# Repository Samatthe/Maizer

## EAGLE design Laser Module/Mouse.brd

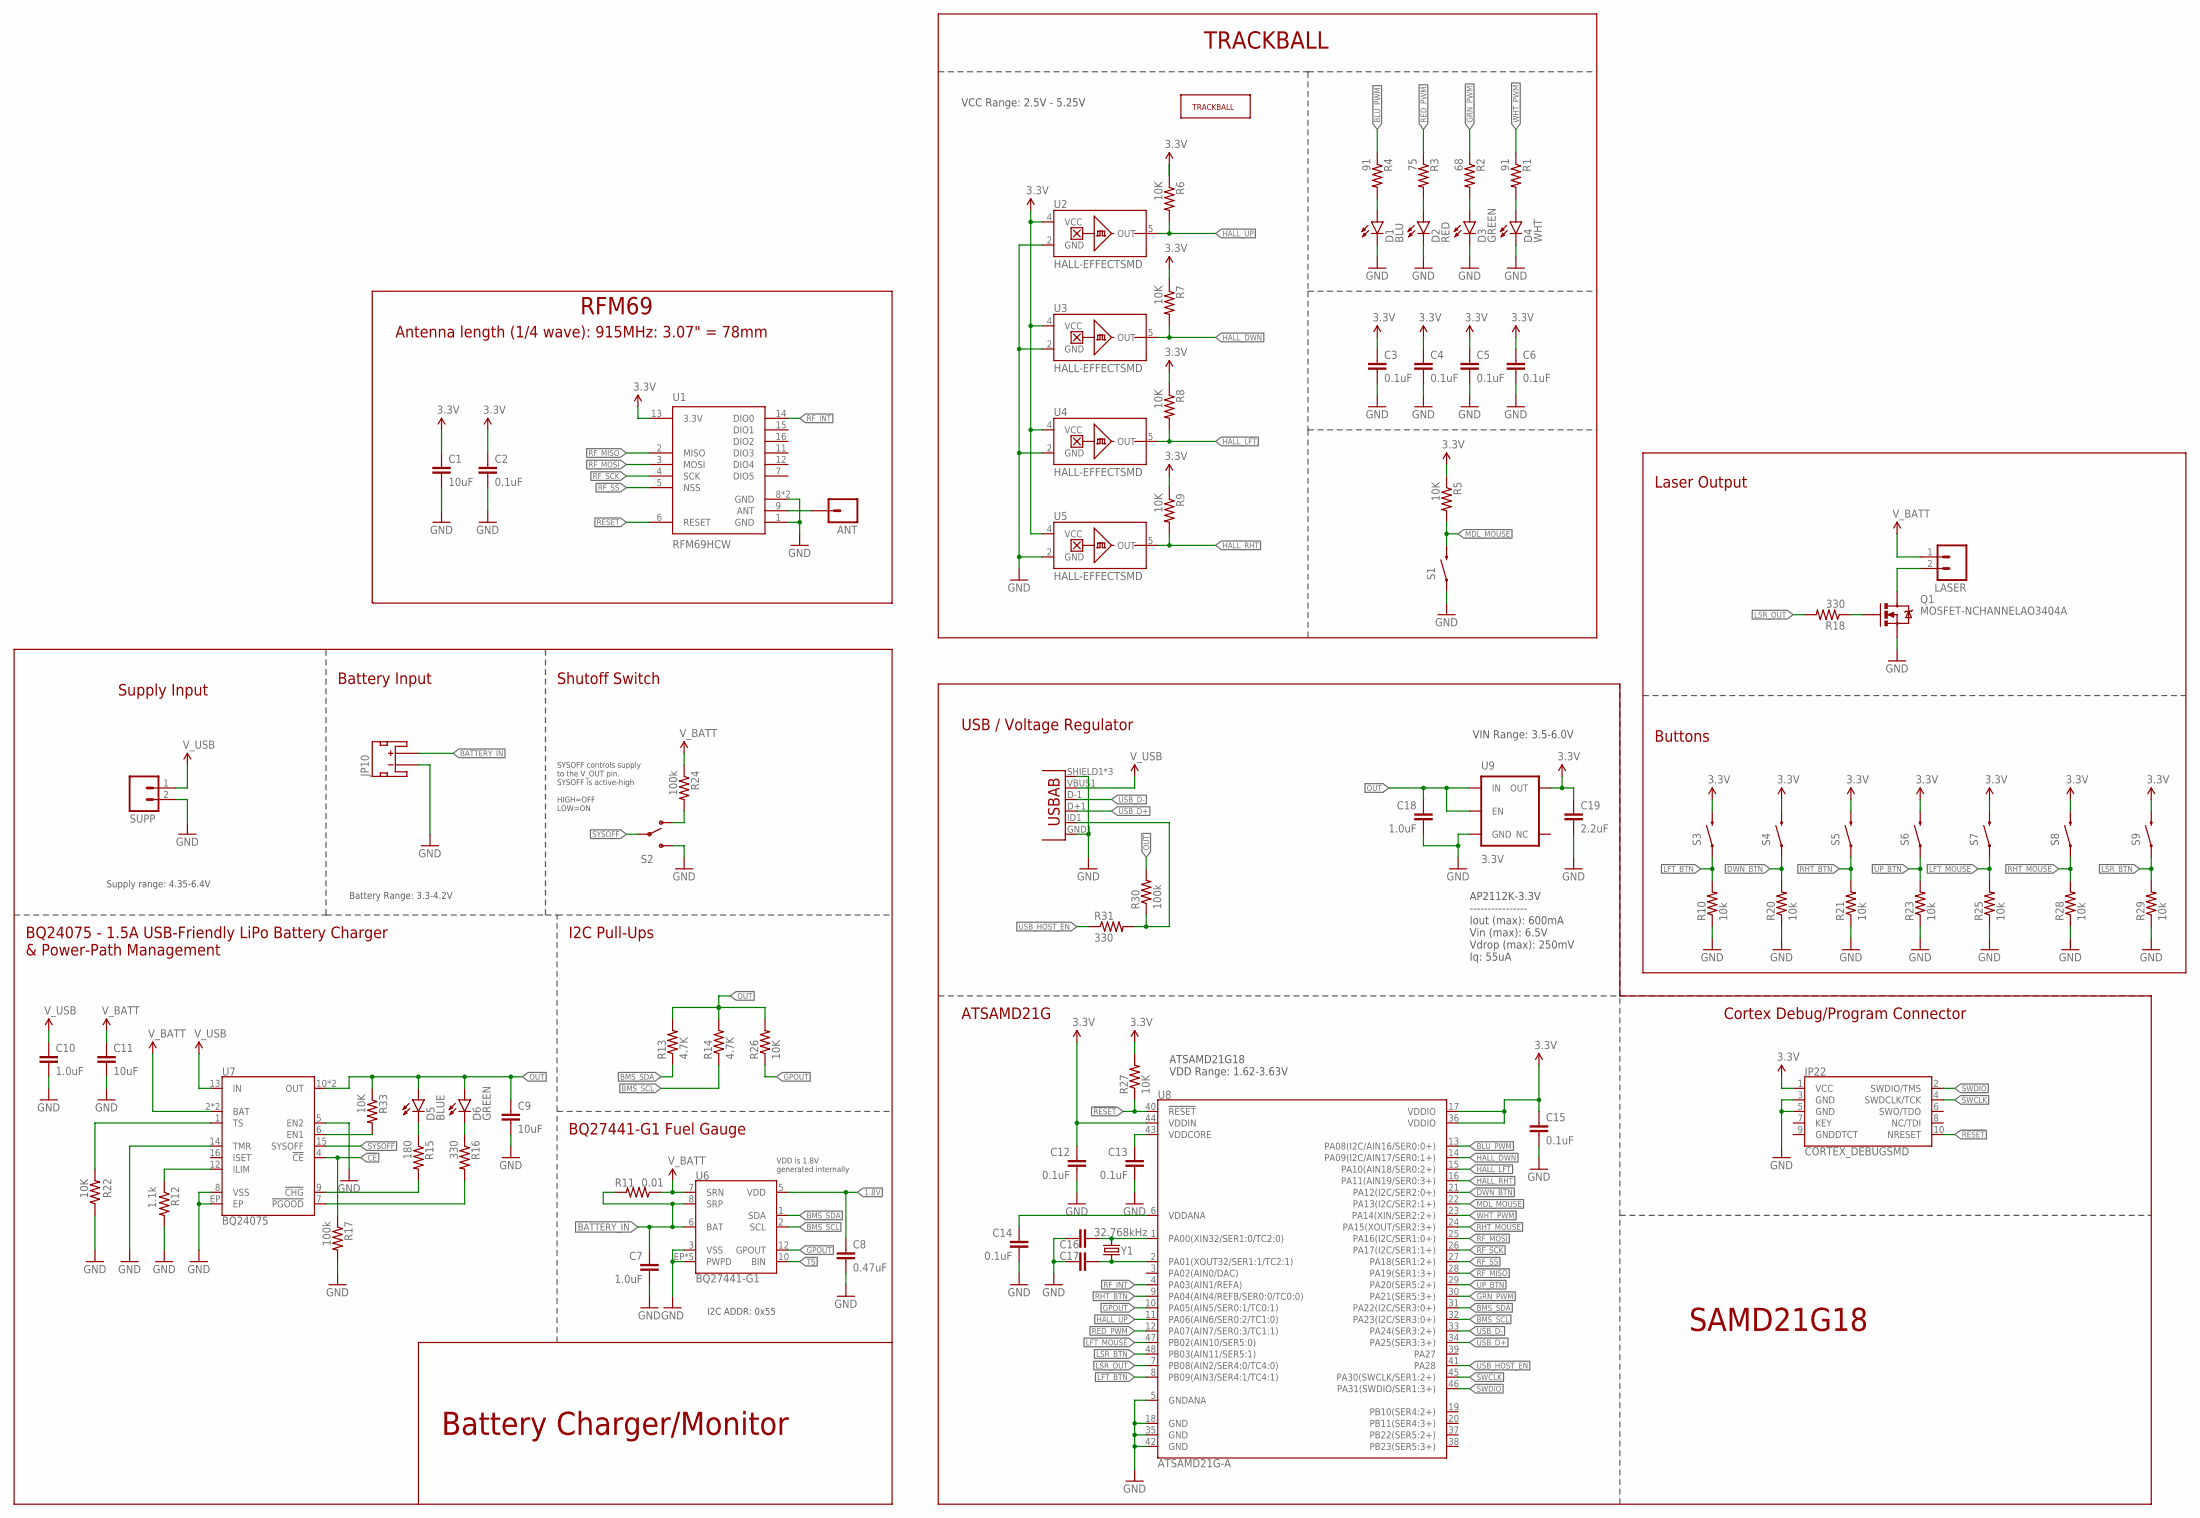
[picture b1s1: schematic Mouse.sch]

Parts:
ANT: M01PTH_NO_SILK_YES_STOP; 1X01_NO_SILK
C1: 10uF; 1210
C2, C3, C4, C5, C6, C12, C13, C14, C15: 0.1uF; 0603-CAP
C7: 1.0uF; 0603-CAP
C8: 0.47uF; 0603-CAP
C9, C11: 10uF; 0805-CAP
C10: 1.0uF; 1206-CAP
C16, C17: 15pF; 0603-CAP
C18: 1.0uF; 0805-CAP
C19: 2.2uF; 0603-CAP
D1: BLU; LED-0603
D2: RED; LED-0603
D3, D6: GREEN; LED-0603
D4: WHT; LED-0603
D5: BLUE; LED-0603
JP10: JST_2MM_MALE; JST-2-SMD
JP22: CORTEX_DEBUGSMD; SAMTECH_FTSH-105-01
JP23: USB-ABCONN-11794; USB-AB-MICRO-SMD_V03
LASER: M021X02_NO_SILK; 1X02_NO_SILK
Q1: MOSFET-NCHANNELAO3404A; SOT23-3
R1, R4: 91; 0603-RES@2
R2: 68; 0603-RES@2
R3: 75; 0603-RES@2
R5, R6, R7, R8, R9: 10K; 0603-RES@1
R10, R20, R21, R23, R25, R28, R29: 10k; 0603-RES
R11: 0.01; 1206
R12: 1.1k; 0603-RES
R13, R14: 4.7K; 0603-RES@2
R15: 180; 0603-RES@2
R16: 330; 0603-RES@2
R17, R24, R30: 100k; 0603-RES
R18, R31: 330; 0603-RES
R22, R26, R27, R33: 10K; 0603-RES
S1: SWITCH-MOMENTARY-2SMD-2; TACTILE_SWITCH_SMD-2
S2: SWITCH-SPDT-SMD-A; SWITCH-SPST-SMD-A
S3, S4, S5, S6, S7, S8, S9: SWITCH-MOMENTARY-2SMD-4; TACTILE_SWITCH_TALL
SUPP: M021X02_NO_SILK; 1X02_NO_SILK
U1: RFM69HCW; RFM69HCW-XXXS2
U2, U3, U4, U5: HALL-EFFECTSMD; SC70
U6: BQ27441-G1; PDSO-N12
U7: BQ24075; PVQFN-N16
U8: ATSAMD21G-A; TQFP-48
U9: 3.3V; SOT23-5
U$1: TRACKBALLMECH; TRACKBALL
Y1: 32.768kHz; CRYSTAL-SMD-3.2X1.5MM

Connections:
1.8V: C8.1, U6.5 (VDD)
3.3V: C1.1, C2.1, C3.1, C4.1, C5.1, C6.1, C12.1, C15.1, C19.1, JP22.1 (VCC), R5.1, R6.1, R7.1, R8.1, R9.1, R27.2, S3.B2 (2), S4.B2 (2), S5.B2 (2), S6.B2 (2), S7.B2 (2), S8.B2 (2), S9.B2 (2), U1.13 (3.3V), U2.4 (VCC), U3.4 (VCC), U4.4 (VCC), U5.4 (VCC), U8.17 (VDDIO), U8.36 (VDDIO), U8.44 (VDDIN), U9.5 (OUT)
!CE!: R17.1, U7.4 (!CE!)
!CHG!: R15.2, U7.9 (!CHG!)
!PGOOD!: R16.2, U7.7 (!PGOOD!)
!RESET: JP22.10 (NRESET), R27.1, U8.40 (!RESET!)
ANT: ANT.1, U1.9 (ANT)
BATTERY_IN: C7.1, JP10.2 (+), R11.2, U6.6 (BAT), U6.8 (SRP)
BLU_PWM: R4.1, U8.13 (PA08(I2C/AIN16/SER0:0+))
BMS_SCL: R14.1, U6.2 (SCL), U8.32 (PA23(I2C/SER3:0+))
BMS_SDA: R13.1, U6.1 (SDA), U8.31 (PA22(I2C/SER3:0+))
DWN_BTN: R20.2, S4.A2 (1), U8.21 (PA12(I2C/SER2:0+))
EN1: R33.2, U7.6 (EN1)
GND: C1.2, C2.2, C3.2, C4.2, C5.2, C6.2, C7.2, C8.2, C9.2, C10.2, C11.2, C12.2, C13.2, C14.2, C15.2, C16.1, C17.2, C18.2, C19.2, D1.C, D2.C, D3.C, D4.C, JP10.1 (-), JP22.3 (GND), JP22.5 (GND), JP23.GND1 (GND), JP23.SHIELD1 (SHIELD), JP23.SHIELD2 (SHIELD), JP23.SHIELD3 (SHIELD), Q1.2 (S), R10.1, R12.2, R17.2, R20.1, R21.1, R22.1, R23.1, R25.1, R28.1, R29.1, S1.2 (1), S2.3 (S), SUPP.2, U1.1 (GND), U1.8 (GND), U1.10 (GND), U2.2 (GND), U3.2 (GND), U4.2 (GND), U5.2 (GND), U6.3 (VSS), U6.EP (PWPD), U6.EP1 (PWPD), U6.EP2 (PWPD), U6.EP3 (PWPD), U6.EP4 (PWPD), U7.5 (EN2), U7.8 (VSS), U7.14 (TMR), U7.EP, U8.5 (GNDANA), U8.18 (GND), U8.35 (GND), U8.42 (GND), U9.2 (GND)
GPOUT: R26.1, U6.12 (GPOUT), U8.10 (PA05(AIN5/SER0:1/TC0:1))
GRN_PWM: R2.1, U8.30 (PA21(SER5:3+))
HALL_DWN: R7.2, U3.5 (OUT), U8.14 (PA09(I2C/AIN17/SER0:1+))
HALL_LFT: R8.2, U4.5 (OUT), U8.15 (PA10(AIN18/SER0:2+))
HALL_RHT: R9.2, U5.5 (OUT), U8.16 (PA11(AIN19/SER0:3+))
HALL_UP: R6.2, U2.5 (OUT), U8.11 (PA06(AIN6/SER0:2/TC1:0))
ILIM: R12.1, U7.12 (ILIM)
LFT_BTN: R10.2, S3.A2 (1), U8.8 (PB09(AIN3/SER4:1/TC4:1))
LFT_MOUSE: R25.2, S7.A2 (1), U8.47 (PB02(AIN10/SER5:0))
LSR_BTN: R29.2, S9.A2 (1), U8.48 (PB03(AIN11/SER5:1))
LSR_OUT: R18.2, U8.7 (PB08(AIN2/SER4:0/TC4:0))
MDL_MOUSE: R5.2, S1.1 (2), U8.22 (PA13(I2C/SER2:1+))
unnamed: D3.A, R2.2
unnamed: D2.A, R3.2
unnamed: D1.A, R4.2
unnamed: D4.A, R1.2
unnamed: R24.2, S2.1 (O)
unnamed: Q1.1 (G), R18.1
unnamed: LASER.2, Q1.3 (D)
unnamed: C16.2, U8.1 (PA00(XIN32/SER1:0/TC2:0)), Y1.P$2 (2)
unnamed: D5.C, R15.1
unnamed: D6.C, R16.1
unnamed: C17.1, U8.2 (PA01(XOUT32/SER1:1/TC2:1)), Y1.P$1 (1)
unnamed: JP23.ID1 (USBID), R30.1, R31.2
OUT: C9.1, C18.1, D5.A, D6.A, R13.2, R14.2, R26.2, R30.2, R33.1, U7.10 (OUT), U7.11 (OUT), U9.1 (IN), U9.3 (EN)
RED_PWM: R3.1, U8.12 (PA07(AIN7/SER0:3/TC1:1))
RESET: U1.6 (RESET)
RF_INT: U1.14 (DIO0), U8.4 (PA03(AIN1/REFA))
RF_MISO: U1.2 (MISO), U8.28 (PA19(SER1:3+))
RF_MOSI: U1.3 (MOSI), U8.25 (PA16(I2C/SER1:0+))
RF_SCK: U1.4 (SCK), U8.26 (PA17(I2C/SER1:1+))
RF_SS: U1.5 (NSS), U8.27 (PA18(SER1:2+))
RHT_BTN: R21.2, S5.A2 (1), U8.9 (PA04(AIN4/REFB/SER0:0/TC0:0))
RHT_MOUSE: R28.2, S8.A2 (1), U8.24 (PA15(XOUT/SER2:3+))
SWCLK: JP22.4 (SWDCLK/TCK), U8.45 (PA30(SWCLK/SER1:2+))
SWDIO: JP22.2 (SWDIO/TMS), U8.46 (PA31(SWDIO/SER1:3+))
SYSOFF: S2.2, U7.15 (SYSOFF)
TS: R22.2, U6.10 (BIN), U7.1 (TS)
UP_BTN: R23.2, S6.A2 (1), U8.29 (PA20(SER5:2+))
USB_D+: JP23.D+1 (D+), U8.34 (PA25(SER3:3+))
USB_D-: JP23.D-1 (D-), U8.33 (PA24(SER3:2+))
USB_HOST_EN: R31.1, U8.41 (PA28)
VDDANA: C14.1, U8.6 (VDDANA)
VDDCORE: C13.1, U8.43 (VDDCORE)
V_BATT: C11.1, LASER.1, R11.1, R24.1, U6.7 (SRN), U7.2 (BAT), U7.3 (BAT)
V_USB: C10.1, JP23.VBUS1 (VBUS), SUPP.1, U7.13 (IN)
WHT_PWM: R1.1, U8.23 (PA14(XIN/SER2:2+))

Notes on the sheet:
Antenna length (1/4 wave): 915MHz: 3.07" = 78mm
RFM69
VCC Range: 2.5V - 5.25V
TRACKBALL
Supply Input
Battery Input
Shutoff Switch
BQ24075 - 1.5A USB-Friendly LiPo Battery Charger & Power-Path Management
I2C Pull-Ups
BQ27441-G1 Fuel Gauge
SYSOFF controls supply to the V_OUT pin. SYSOFF is active-high HIGH=OFF LOW=ON
Supply range: 4.35-6.4V
VDD is 1.8V generated internally
I2C ADDR: 0x55
Battery Range: 3.3-4.2V
Battery Charger/Monitor
USB / Voltage Regulator
Buttons
Cortex Debug/Program Connector
ATSAMD21G
ATSAMD21G18 VDD Range: 1.62-3.63V
VIN Range: 3.5-6.0V
AP2112K-3.3V ---------------- Iout (max): 600mA Vin (max): 6.5V Vdrop (max): 250mV Iq: 55uA
SAMD21G18
Laser Output

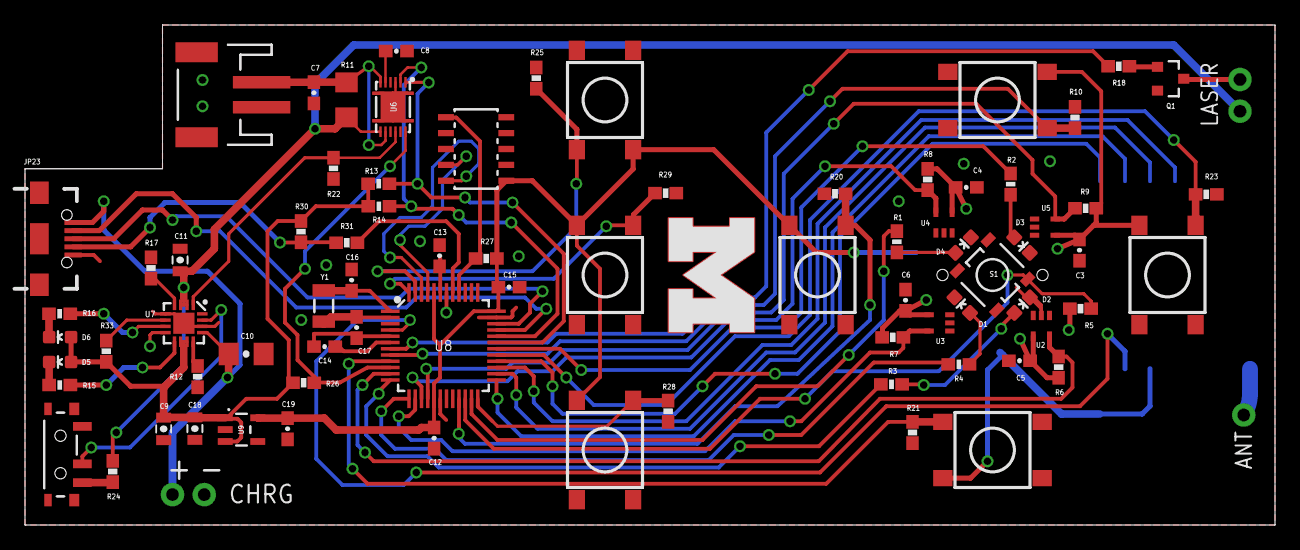
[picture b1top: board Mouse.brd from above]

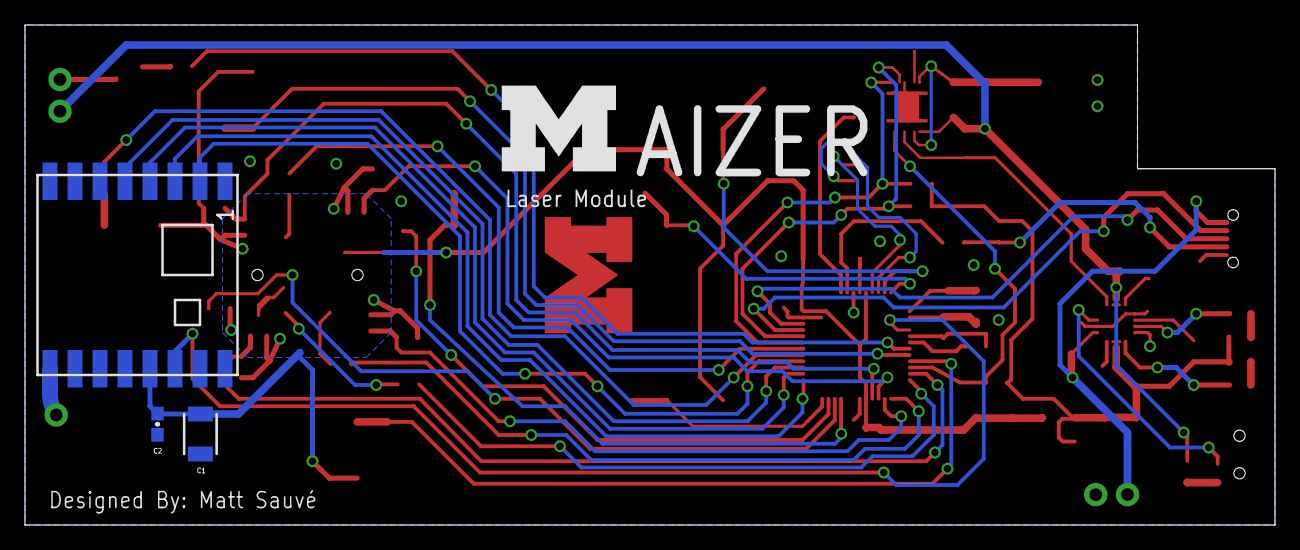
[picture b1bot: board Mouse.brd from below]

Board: 2 copper layers, 100.0 x 40.0 mm, 85 parts (4 on the bottom side), 60 nets.

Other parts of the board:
U$2: BLOCK-M-10MM
U$3: BLOCK-M-10MM-MASK

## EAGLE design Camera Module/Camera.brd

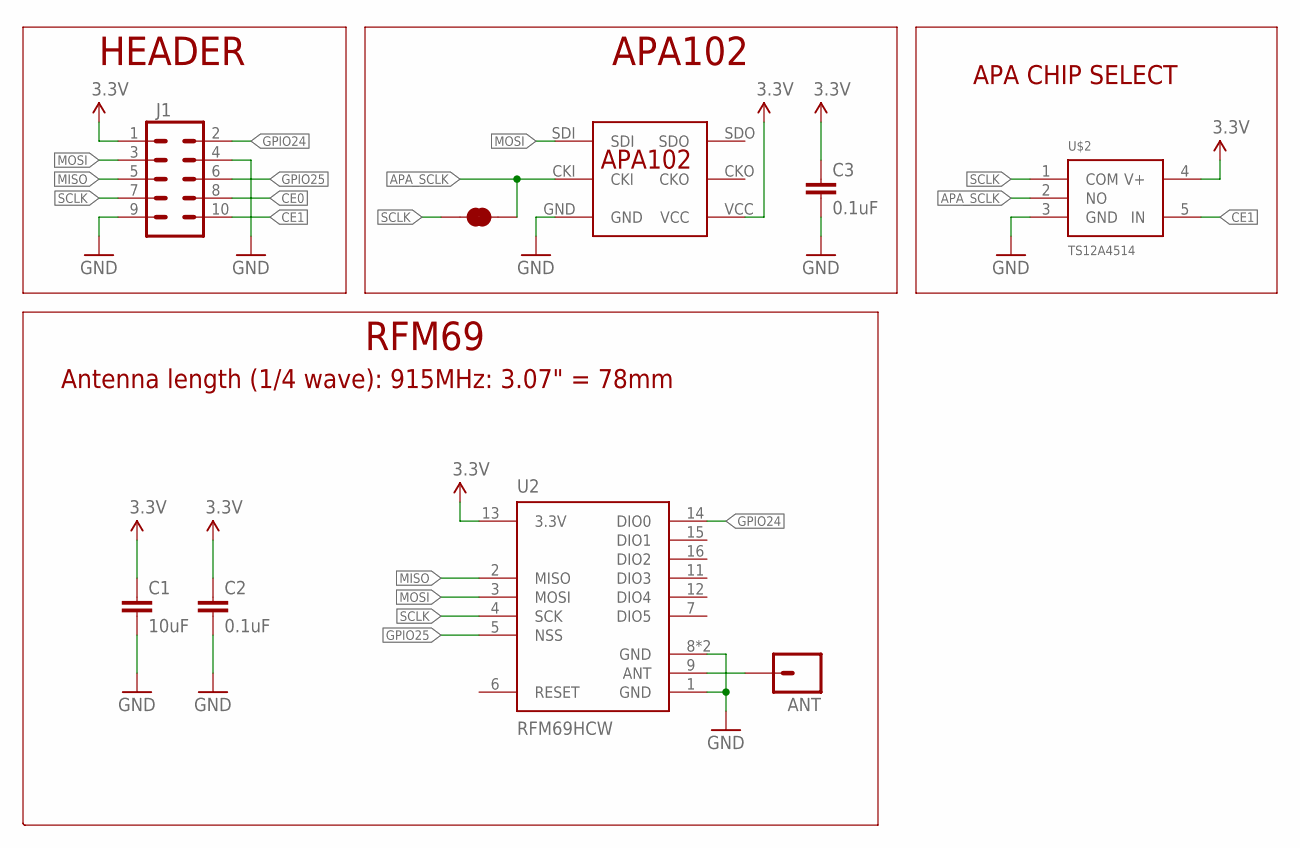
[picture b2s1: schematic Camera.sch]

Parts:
ANT: M01PTH_NO_SILK_YES_STOP; 1X01_NO_SILK
C1: 10uF; 1210
C2, C3: 0.1uF; 0603-CAP@1
J1: M05X2NO_SILK; 2X5_NOSILK
JP1: JUMPER-PAD-2-NC_BY_TRACE; PAD-JUMPER-2-NC_BY_TRACE_YES_SILK
U2: RFM69HCW; RFM69HCW-XXXS2
U$1: APA102
U$2: TS12A4514; SOT-23

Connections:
3.3V: C1.1, C2.1, C3.1, J1.1, U2.13 (3.3V), U$1.VCC, U$2.4 (V+)
ANT: ANT.1, U2.9 (ANT)
APA_SCLK: JP1.2, U$1.CKI, U$2.2 (NO)
CE0: J1.8
CE1: J1.10, U$2.5 (IN)
GND: C1.2, C2.2, C3.2, J1.4, J1.9, U2.1 (GND), U2.8 (GND), U2.10 (GND), U$1.GND, U$2.3 (GND)
GPIO24: J1.2, U2.14 (DIO0)
GPIO25: J1.6, U2.5 (NSS)
MISO: J1.5, U2.2 (MISO)
MOSI: J1.3, U2.3 (MOSI), U$1.SDI
SCLK: J1.7, JP1.1, U2.4 (SCK), U$2.1 (COM)

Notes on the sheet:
Antenna length (1/4 wave): 915MHz: 3.07" = 78mm
RFM69
HEADER
APA102
APA CHIP SELECT

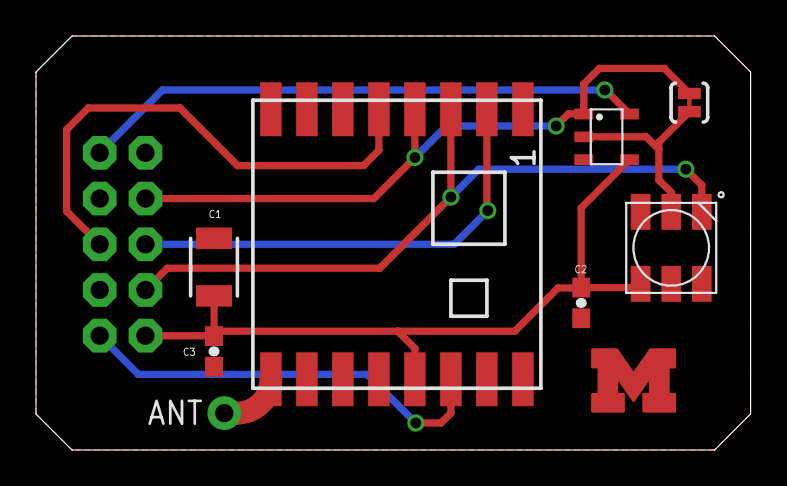
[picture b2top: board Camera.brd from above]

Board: 2 copper layers, 39.7 x 23.0 mm, 11 parts (1 on the bottom side), 10 nets.

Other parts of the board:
U$3: BLOCK-M-5MM-MASK
U$5: BLOCK-M-10MM

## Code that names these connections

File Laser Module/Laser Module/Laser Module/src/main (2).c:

/**
 * \file
 *
 * \brief Empty user application template
 *
 */

/**
 * \mainpage User Application template doxygen documentation
 *
 * \par Empty user application template
 *
 * Bare minimum empty user application template
 *
 * \par Content
 *
 * -# Include the ASF header files (through asf.h)
 * -# Minimal main function that starts with a call to system_init()
 * -# "Insert application code here" comment
 *
 */

/*
 * Include header files for all drivers that have been imported from
 * Atmel Software Framework (ASF).
 */
/*
 * Support and FAQ: visit <a href="http://www.atmel.com/design-support/">Atmel Support</a>
 */
#include <asf.h>
#include <inttypes.h>
#include "RFM69.h"
#include "BQ27441.h"
#include "wheel.h"

// Addresses for this node.
#define NETWORKID     0   // Must be the same for all nodes (0 to 255)
#define MYNODEID      3   // My node ID (0 to 255)
#define TONODEID      2   // Destination node ID (0 to 254, 255 = broadcast)

// RFM69 frequency:
#define FREQUENCY     RF69_915MHZ

// AES encryption:
#define ENCRYPT       true // Set to "true" to use encryption
#define ENCRYPTKEY    "TOPSECRETPASSWRD" // Use the same 16-byte key on all nodes

// Use ACKnowledge when sending messages:
#define USEACK        false

// Battery Capacity
#define Capacity 1200

//button to reg value map
//#define 
//#define
//#define 

// Initialization functions
void configure_LED_PWM(void);
struct tcc_module tcc0;
struct tcc_module tcc1;
void configure_IO_pins(void);

// Helper Functions
void ColorCycle(void);

// Helper functions
void setTrackBallRGBW(uint16_t red, uint16_t green, uint16_t blue, uint16_t white);


////////////// Configure all of the LED ports as PWM outputs //////////////////
void configure_LED_PWM(void)
{
	struct tcc_config config_tcc;
	tcc_get_config_defaults(&config_tcc, TCC0);
	config_tcc.counter.period = 0xFFFF;
	config_tcc.compare.wave_generation = TCC_WAVE_GENERATION_SINGLE_SLOPE_PWM;
	config_tcc.compare.match[0] = 0;
	config_tcc.compare.match[1] = 0;
	config_tcc.pins.enable_wave_out_pin[0] = true;
	config_tcc.pins.enable_wave_out_pin[1] = true;
	// Green Trackball LED*
	config_tcc.pins.wave_out_pin[0]        = PIN_PA21F_TCC0_WO7;
	// White Trackball LED*
	config_tcc.pins.wave_out_pin[1]        = PIN_PA14F_TCC0_WO4;
	config_tcc.pins.wave_out_pin_mux[0]    = MUX_PA21F_TCC0_WO7;
	config_tcc.pins.wave_out_pin_mux[1]    = MUX_PA14F_TCC0_WO4;
	tcc_init(&tcc0, TCC0, &config_tcc);
	tcc_enable(&tcc0);

	tcc_get_config_defaults(&config_tcc, TCC1);
	config_tcc.counter.period = 0xFFFF;
	config_tcc.compare.wave_generation = TCC_WAVE_GENERATION_SINGLE_SLOPE_PWM;
	config_tcc.compare.match[0] = 0;
	config_tcc.compare.match[1] = 0;
	config_tcc.pins.enable_wave_out_pin[0] = true;
	config_tcc.pins.enable_wave_out_pin[1] = true;
	// Blue Trackball LED*
	config_tcc.pins.wave_out_pin[0]        = PIN_PA08F_TCC1_WO2;
	// Red Trackball LED*
	config_tcc.pins.wave_out_pin[1]        = PIN_PA07E_TCC1_WO1;
	config_tcc.pins.wave_out_pin_mux[0]    = MUX_PA08F_TCC1_WO2;
	config_tcc.pins.wave_out_pin_mux[1]    = MUX_PA07E_TCC1_WO1;
	tcc_init(&tcc1, TCC1, &config_tcc);
	tcc_enable(&tcc1);
}
///////////////////////////////////////////////////////////////////////////

// Configure the LED selection port as output
void configure_IO_pins(void)
{
	struct port_config config_port_pin;
	port_get_config_defaults(&config_port_pin);
	config_port_pin.direction = PORT_PIN_DIR_INPUT;
	// Right Arrow Button
	port_pin_set_config(PIN_PA04, &config_port_pin);
	// Hall Up*
	port_pin_set_config(PIN_PA06, &config_port_pin);
	// Hall Down*
	port_pin_set_config(PIN_PA09, &config_port_pin);
	// Hall Left*
	port_pin_set_config(PIN_PA10, &config_port_pin);
	// Hall Right*
	port_pin_set_config(PIN_PA11, &config_port_pin);
	// Down Arrow Button
	port_pin_set_config(PIN_PA12, &config_port_pin);
	// Scroll Button
	port_pin_set_config(PIN_PA13, &config_port_pin);
	// Right Mouse Button
	port_pin_set_config(PIN_PA15, &config_port_pin);
	// Up Arrow Button
	port_pin_set_config(PIN_PA20, &config_port_pin);
	// Left Mouse Button
	port_pin_set_config(PIN_PB02, &config_port_pin);
	// Laser Button
	port_pin_set_config(PIN_PB03, &config_port_pin);
	// Left Arrow Button
	port_pin_set_config(PIN_PB09, &config_port_pin);
	// Laser Output
	config_port_pin.direction = PORT_PIN_DIR_OUTPUT;
	port_pin_set_config(PIN_PB08, &config_port_pin);
}


int main (void)
{
	int receivingNode = 0;
	bool calibrationLEDS = false;
	
    /* Initialize system */
	system_init();
	configure_LED_PWM();
	configure_IO_pins();
	

	/*if(!lipo_begin())
	{
		setTrackBallRGBW(0, 0xFFFF, 0, 0);
		
		for(int i = 0; i < 100000; i++)
		{ }
	}
	else
	{
		setTrackBallRGBW(0xFFFF, 0, 0, 0);
	}
	//lipo_setCapacity(Capacity);

	/*uint16_t soc = lipo_soc(FILTERED);
	uint16_t volts = lipo_voltage();
	int16_t current = lipo_current(AVG);
	uint16_t totalCapacity = lipo_capacity(FULL);
	uint16_t remainingCapacity = lipo_capacity(REMAIN);
	int16_t power = lipo_power();
	uint8_t health = lipo_soh(PERCENT);*/

	/*uint16_t timeout = 0;

	struct i2c_master_packet packet = {
		.address     = SLAVE_ADDRESS,
		.data_length = DATA_LENGTH,
		.data        = write_buffer,
		.ten_bit_address = false,
		.high_speed      = false,
		.hs_master_code  = 0x0,
	};

	while (i2c_master_write_packet_wait(&i2c_master_instance, &packet) !=
	STATUS_OK) {
		if (timeout++ == TIMEOUT) {
			break;
		}
	}
	packet.data = read_buffer;
	while (i2c_master_read_packet_wait(&i2c_master_instance, &packet) !=
	STATUS_OK) {
		if (timeout++ == TIMEOUT) {
			break;
		}
	}*/

	// Initialize the RFM69HCW:
	RFM_initialize(FREQUENCY, MYNODEID, NETWORKID);
	RFM_setHighPower(true);
	if (ENCRYPT)
		RFM_encrypt(ENCRYPTKEY);


	int sendlength = 3; //number can be increased 
	int index = 0;
	int8_t sendbuffer[16];

	init_wheel();
	
	while(1) //busy loop
	//sends data after receiving a request message from the dongle
	//sends X axis byte, Y axis byte, button byte
	{
		if (calibrationLEDS)
			ColorCycle();
		else
			setTrackBallRGBW(0x0, 0x0, 0x0, 0xFFFF);
			
		static bool button = 0;
		static bool lbutton = 0;
		static bool laserState = 0;

		button = port_pin_get_input_level(PIN_PB03);
		if(button && !lbutton)
		{
			laserState = !laserState;
			port_pin_set_output_level(PIN_PB08, laserState);
		}

		//Do the wheel update
		update_values();
		
		//getScroll(&sendbuffer[0], &sendbuffer[1]); // x and y axis update
		
		lbutton = button;
		//check if the RFM69 receives a  packet
		//only send info when a packet is received from dongle module			
		if (RFM_receiveDone()) // Got one!
		{
			receivingNode = RFM_SENDERID;
			if (RFM_DATA[0] == 'Y')
				calibrationLEDS = true;
			if (RFM_DATA[0] == 'N')
				calibrationLEDS = false;
			// The actual message is contained in the RFM_DATA array,
			// and is RFM_DATALEN bytes in size:
			getScroll(&sendbuffer[0], &sendbuffer[1]); // x and y axis update

			sendbuffer[2] = 0;
			sendbuffer[2] |= (port_pin_get_input_level(PIN_PA20) << 7); // Up
			sendbuffer[2] |= (port_pin_get_input_level(PIN_PA12) << 6); // Down
			sendbuffer[2] |= (port_pin_get_input_level(PIN_PB09) << 5); // Left
			sendbuffer[2] |= (port_pin_get_input_level(PIN_PA15) << 4); // Right
			sendbuffer[2] |= (port_pin_get_input_level(PIN_PB02) << 3); // Left Click
			sendbuffer[2] |= (port_pin_get_input_level(PIN_PA15) << 2); // Right Click
			sendbuffer[2] |= (port_pin_get_input_level(PIN_PA13) << 1); // Middle Click
			sendbuffer[2] |= laserState;								// Laser State

			RFM_send(receivingNode, sendbuffer, sendlength, false);
		}
	}
}

void setTrackBallRGBW(uint16_t red, uint16_t green, uint16_t blue, uint16_t white)
{	
	/* WHITE */
	tcc_set_compare_value(&tcc0, (enum tcc_match_capture_channel) (0), white);
	/* GREEN */
	tcc_set_compare_value(&tcc0, (enum tcc_match_capture_channel) (3), green);
	/* BLUE */
	tcc_set_compare_value(&tcc1, (enum tcc_match_capture_channel) (0), blue);
	/* RED */
	tcc_set_compare_value(&tcc1, (enum tcc_match_capture_channel) (1), red);
} 

void ColorCycle(void)
{
	static int color = 0;
	static int speed = 100;
	static int index = 0;
	if(index == 0)
	{
		setTrackBallRGBW(0xFFFF - color,color,0x0,0x0);
	}
	else if(index == 1)
	{
		setTrackBallRGBW(0x0,0xFFFF - color,color,0x0);
	}
	else if(index == 2)
	{
		setTrackBallRGBW(color,0x0,0xFFFF - color,0x0);
	}
	
	color += speed;
	if(color >= 0xFFFF)
	{
		color = 0;
		index++;
		if(index > 2)
		index = 0;
	}
}

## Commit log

2016-10-11 Initial creation of the repo
2016-10-11 Added dongle and laser folders
2016-10-13 Added starter files for the dongle and laser modules
2016-10-13 Added RFM69 code to laser code
2016-10-17 Started mouse schematic
2016-10-17 Updated Mouse schematic Created mouse board file Created dongle schematic and board files based off the mouse files
2016-10-17 Worked on the laser and dongle schematics Placed the parts on the laser and dongle boards in their rough locations
2016-10-23 Created, placed, and routed a starter board for the Camera Module
2016-10-24 Routed the dongle and camera modules
2016-10-26 Created starter files for the RFM69 library used on the laser module
2016-10-26 Updated the RFM69 library to be closer to C and editted the arduino example code to be closer to a C Pi program and a C SAMD21 program
2016-10-26 Added the interrupt line from the RFM69 into the Camera Module board. It is connected to GPIO_24
2016-10-27 Add base RFM69 files to camera module. These will be modified to work with RBP's SPI.
2016-10-27 rewrite Pi_example for c++
2016-10-27 fixed a lot of compilation issues
2016-10-27 Created starter SAMD projects for the laser and dongle modules
2016-10-27 example should work. Library port still a work in progress
2016-10-28 Updated the RFM69 library to be closer to C. millis() is the only function hat needs to be updated now.
2016-10-29 add millis function
2016-10-29 enters infinite loop at readReg
2016-11-01 Got the RFM69 library partially working for the SAMD21
2016-11-01 Continued work on the RFM69 library for SAMD21
2016-11-04 sending on Pi works
2016-11-04 clean code up a bit
2016-11-04 Started the routing of the laser module board Updated the Dongle Module C project to allow for absolute mouse control
2016-11-05 Finished routing the laser module
2016-11-05 Update the camera module board to include a chip select line for the APA102 and added to the silk screen
2016-11-06 Added text to the Dongle Module board
2016-11-06 Cleaned up and added text to the Laser module silkscreen
2016-11-07 add apa102 code to the example
2016-11-07 Finalized all PCBs
2016-11-08 ACTUALLY finalized all of the PCBs and created .zip's containing the gerber files of each
2016-11-09 Added all of the functions required for interacting with peripherals to the laser and dongle code
2016-11-10 fixup dongle module
2016-11-14 Dongle module issue - lots of multiple definition ofs
2016-11-14 Fix Dongle project so it compiles
2016-11-14 switched to using ui.c
2016-11-14 push ui.c again
2016-11-15 Updated the Dongle project so USB and SPI can be used at the same time
2016-11-17 Updated the laser and dongle projects for developement witht the PCBs
2016-11-17 re-add the radio to laser module
2016-11-22 Added stuffs to the Laser module and Dongle module projects
2016-11-22 update to better radio lib
2016-11-22 Lets try this again
2016-11-23 Added button sending and laser functionality to the laser module project Also fixed the dongle module project slightly
2016-11-27 -Change library file names from caps to lower case -Change paramets such as CSMA limit (raise), and timing limits (lower). -Re-add LED
2016-11-28 Updated the laser and dongle module projects
2016-11-28 Added scroll wheel header and cpp files
2016-11-28 Added some code to main to test compiling
2016-11-28 Added scroll wheel code
2016-11-29 Some additions to the code, modified slightly with wheel Please enter the commit message for your changes. Lines starting
2016-11-29 Updated image projective files, example code
2016-11-29 Some changes to the files with perspective
2016-11-29 Correct perspective test, samples correction code
2016-11-29 Updated the dongle module code to smooth out the mouse control
2016-11-29 Working threaded camera code, main.cpp has all major code
2016-11-29 ready laser module for calibration
2016-11-30 add code to dongle to handle calibration
2016-11-30 Add a function that will nearly drop into the camera module's spi send func
2016-11-30 Changes to wheel to make code work correctly
2016-11-30 Changes to the wheel library
2016-11-30 Camera - working click and movement with xbees
2016-12-01 correct errors in dongle module. Also add double sends
2016-12-02 This commit has the basis of calibration working. Button fixes were applied to laser module. New test.cpp exists in camera module and has an example of how send show (mostly) look now.
2016-12-02 Rewrite the test function to fit the new radio scheme
2016-12-04 dongle module ignores location info when laser is off
2016-12-06 Changes to the battery monitor code
2016-12-06 allow clicks when laser is toggled off
2016-12-07 add new laser module code to show charging
2016-12-07 fix previous push for laser
2016-12-07 WORKING TRACKING AND BUTTON CLICKS @ 10HZ
2016-12-08 Changed laser and dongle modules night due (partially working)
2016-12-08 THIS SHIT WORKS
2016-12-19 Updated laser module code, for Matt

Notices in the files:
parts and their libraries:
SparkFun-Connectors: Licensing: Creative Commons ShareAlike 4.0 International - https://creativecommons.org/licenses/by-sa/4.0
SparkFun-Capacitors: Licensing: CC v3.0 Share-Alike You are welcome to use this library for commercial purposes.
